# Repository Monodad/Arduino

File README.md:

# Arduino

我單純只是想做個紀錄而已，要不然每次都把檔案用不見 QAQ

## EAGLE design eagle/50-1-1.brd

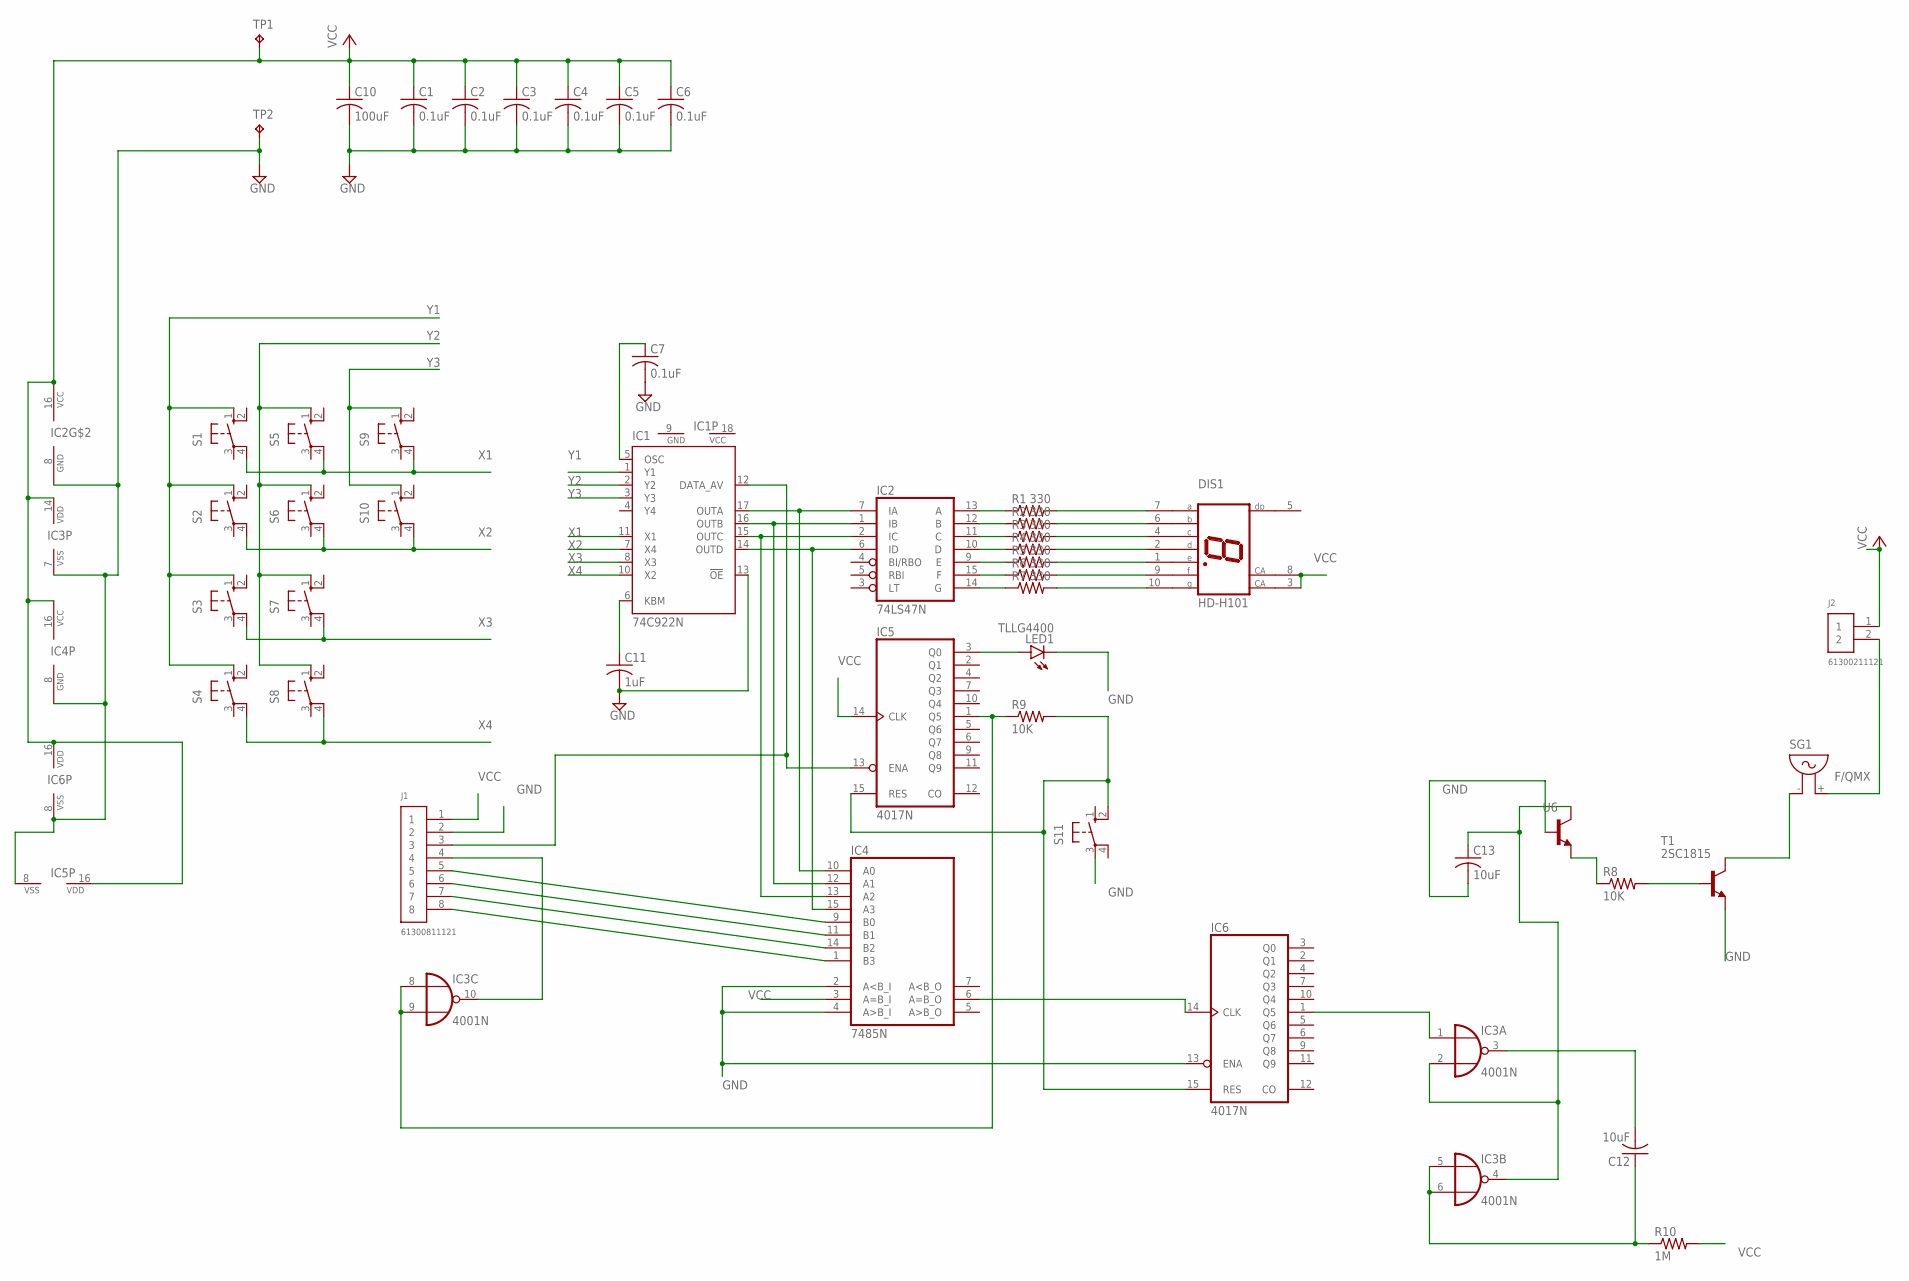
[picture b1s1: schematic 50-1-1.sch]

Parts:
C1, C2, C3, C4, C5, C6, C7: 0.1uF; C050-024X044
C10: 100uF; C025-050X050
C11: 1uF; C025-050X050
C12, C13: 10uF; C025-050X050
DIS1: HD-H101; HDSP-M
IC1: 74C922N; DIL18
IC2: 74LS47N; DIL16
IC3: 4001N; DIL14
IC4: 7485N; DIL16
IC5, IC6: 4017N; DIL16
J1: 61300811121
J2: 61300211121
LED1: TLLG4400; LED3MM
R1, R2, R3, R4, R5, R6, R7: 330; 0204/5
R8, R9: 10K; 0204/5
R10: 1M; 0204/5
S1, S2, S3, S4, S5, S6, S7, S8, S9, S10, S11: 10-XX; B3F-10XX
SG1: F/QMX
T1: 2SC1815; TO92-ECB
TP1, TP2: TPPAD1-13; P1-13
U6: -NPN-TO92-BCE; TO92-BCE

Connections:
GND: C1.2, C2.2, C3.2, C4.2, C5.2, C6.2, C7.2, C10.2, C11.2, C13.2, IC1.9 (GND), IC1.13 (!OE), IC2.8 (GND), IC3.7 (VSS), IC4.2 (A<B_I), IC4.4 (A>B_I), IC4.8 (GND), IC5.8 (VSS), IC6.8 (VSS), IC6.13 (ENA), J1.2, LED1.K (C), S11.3, T1.E, TP2.TP, U6.B
unnamed: C11.1, IC1.6 (KBM)
unnamed: C7.1, IC1.5 (OSC)
unnamed: IC1.17 (OUTA), IC2.7 (IA), IC4.10 (A0)
unnamed: IC1.16 (OUTB), IC2.1 (IB), IC4.12 (A1)
unnamed: IC1.15 (OUTC), IC2.2 (IC), IC4.13 (A2)
unnamed: IC1.14 (OUTD), IC2.6 (ID), IC4.15 (A3)
unnamed: IC3.8 (I0), IC3.9 (I1), IC5.1 (Q5), R9.1
unnamed: IC5.3 (Q0), LED1.A
unnamed: IC4.6 (A=B_O), IC6.14 (CLK)
unnamed: IC5.15 (RES), IC6.15 (RES), R9.2, S11.2 (S1)
unnamed: IC3.10 (O), J1.4
unnamed: IC4.1 (B3), J1.8
unnamed: IC4.14 (B2), J1.7
unnamed: IC4.11 (B1), J1.6
unnamed: IC4.9 (B0), J1.5
unnamed: IC1.12 (DATA_AV), IC5.13 (ENA), J1.3
unnamed: IC2.13 (A), R1.1
unnamed: IC2.12 (B), R2.1
unnamed: IC2.11 (C), R3.1
unnamed: IC2.10 (D), R4.1
unnamed: IC2.9 (E), R5.1
unnamed: IC2.15 (F), R6.1
unnamed: IC2.14 (G), R7.1
unnamed: DIS1.7 (A), R1.2
unnamed: DIS1.6 (B), R2.2
unnamed: DIS1.4 (C), R3.2
unnamed: DIS1.2 (D), R4.2
unnamed: DIS1.1 (E), R5.2
unnamed: DIS1.9 (F), R6.2
unnamed: DIS1.10 (G), R7.2
unnamed: IC3.1 (I0), IC6.1 (Q5)
unnamed: C13.1, IC3.2 (I1), IC3.4 (O), U6.C
unnamed: C12.1, IC3.5 (I0), IC3.6 (I1), R10.1
unnamed: C12.2, IC3.3 (O)
unnamed: R8.1, U6.E
unnamed: R8.2, T1.B
unnamed: SG1.- (1), T1.C
unnamed: J2.2, SG1.+ (2)
VCC: C1.1, C2.1, C3.1, C4.1, C5.1, C6.1, C10.1, DIS1.3 (CA), DIS1.8 (CA), IC1.18 (VCC), IC2.16 (VCC), IC3.14 (VDD), IC4.3 (A=B_I), IC4.16 (VCC), IC5.14 (CLK), IC5.16 (VDD), IC6.16 (VDD), J1.1, J2.1, R10.2, TP1.TP
X1: IC1.11 (X1), S1.4 (P1), S5.4 (P1), S9.4 (P1)
X2: IC1.7 (X4), S2.4 (P1), S6.4 (P1), S10.4 (P1)
X3: IC1.8 (X3), S3.4 (P1), S7.4 (P1)
X4: IC1.10 (X2), S4.4 (P1), S8.4 (P1)
Y1: IC1.1 (Y1), S1.1 (S), S2.1 (S), S3.1 (S), S4.1 (S)
Y2: IC1.2 (Y2), S5.1 (S), S6.1 (S), S7.1 (S), S8.1 (S)
Y3: IC1.3 (Y3), S9.1 (S), S10.1 (S)

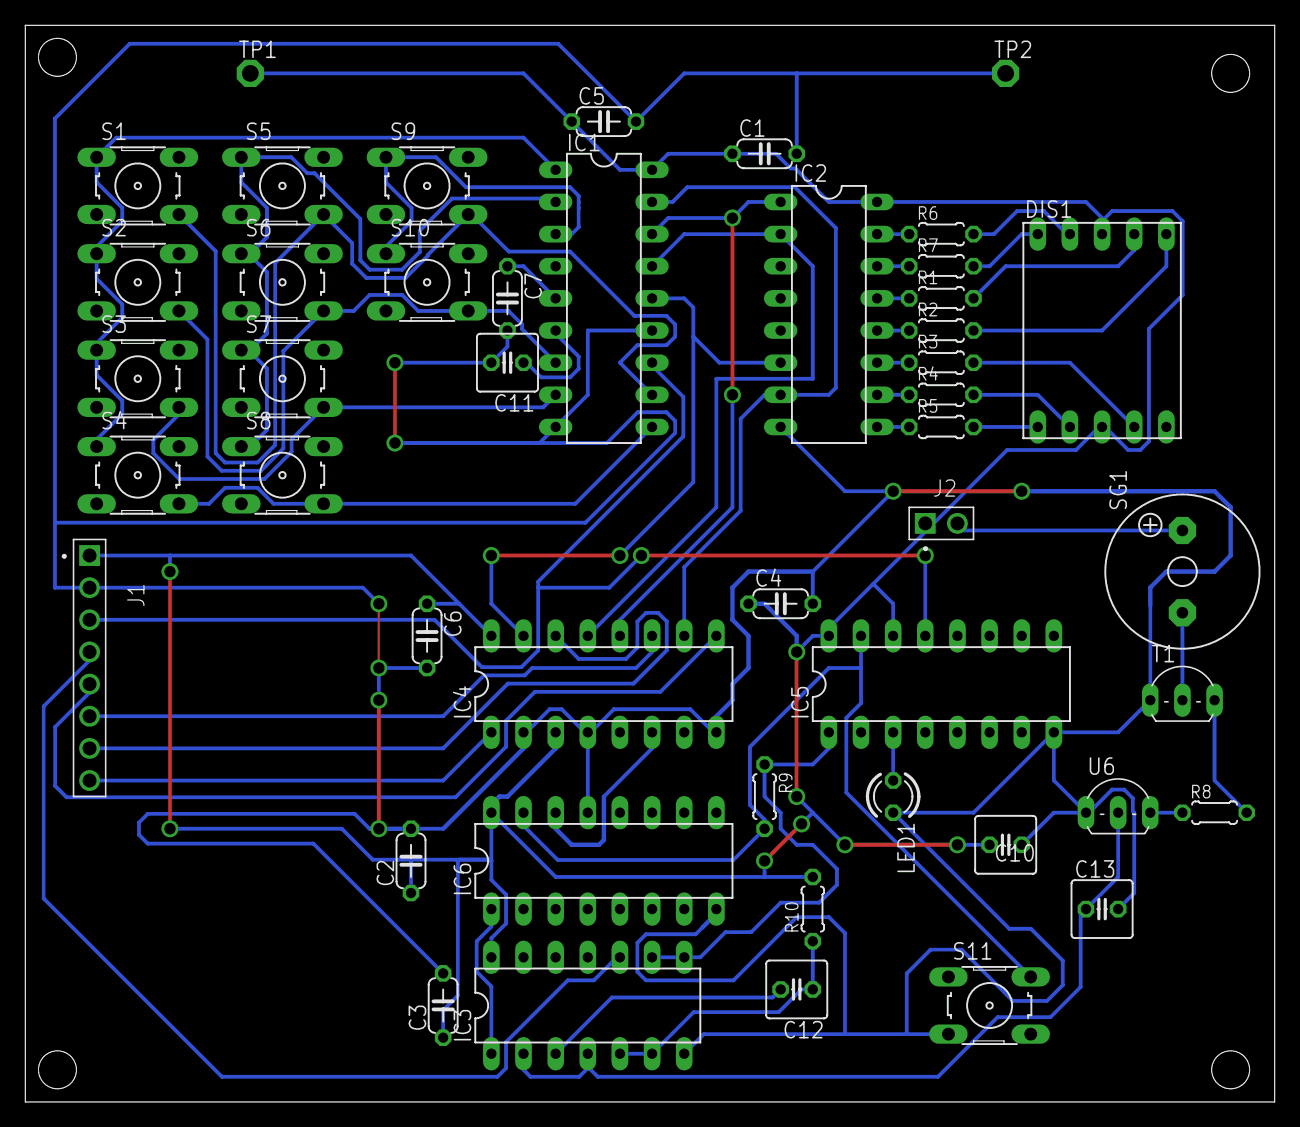
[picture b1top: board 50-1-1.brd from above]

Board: 2 copper layers, 98.7 x 85.1 mm, 47 parts (0 on the bottom side), 47 nets.

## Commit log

2021-09-21 This is the new begining
2021-09-21 GOGO
2021-09-21 test1
2021-09-21 test 2
2021-09-21 arduino build test for VSC
2021-09-21 This is not god
2021-09-21 Test 1
2021-09-21 updata at 2021/9/21
2021-09-22 ADXL345 updata
2021-09-29 Add .vscode to .gitignore
2021-09-29 .vscode files
2021-09-29 remove SECURITY.md
2021-09-29 Formatting
2021-09-30 Remove delays and fix warnings
2021-09-30 Added Untitled Diagram.drawio
2021-09-30 Fix spelling
